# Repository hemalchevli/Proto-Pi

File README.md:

Proto-Pi
========

A simple prototyping board for Raspberry Pi with arduino headers
CC-BY-SA 4.0

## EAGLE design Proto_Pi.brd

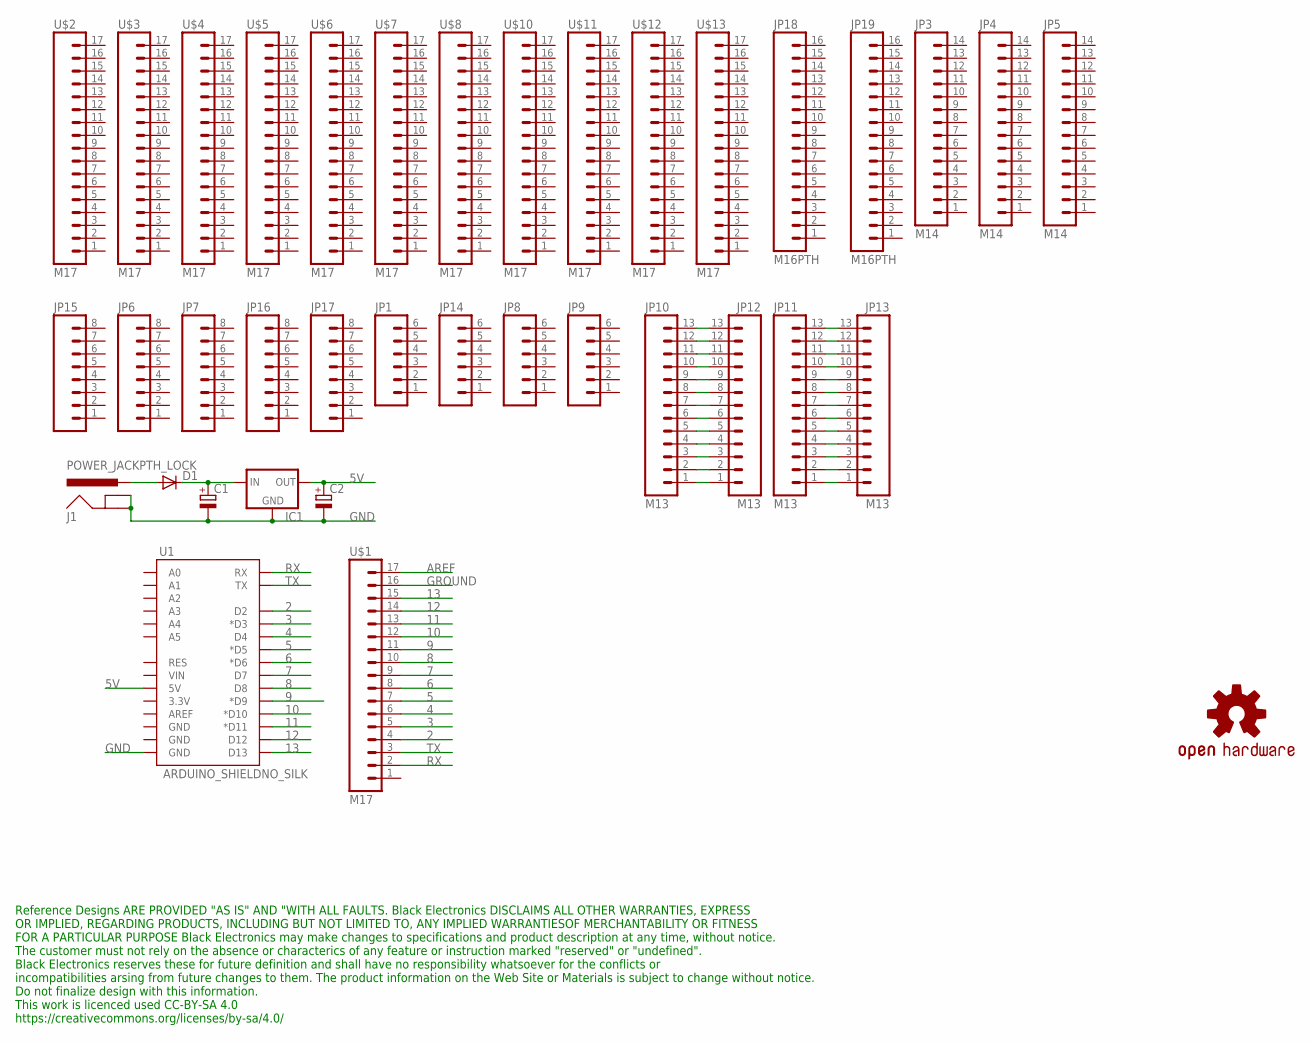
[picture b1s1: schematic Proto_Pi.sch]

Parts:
C1: CPOL-EUE2,5-6E; E2,5-6E
C2: CPOL-EUE2.5-7; E2,5-7
D1: DIODE-C1702-05; C1702-05
IC1: V_REG_78XXSINK; TO220-IGO
J1: POWER_JACKPTH_LOCK; POWER_JACK_PTH_LOCK
JP1, JP8, JP9, JP14: M06SIP; 1X06
JP3, JP4, JP5: M14; 1X14
JP6, JP7, JP15, JP16, JP17: M081X08; 1X08
JP10, JP11, JP12, JP13: M13; 1X13
JP18, JP19: M16PTH; 1X16
U1: ARDUINO_SHIELDNO_SILK; DUEMILANOVE_VIAS
U$1, U$2, U$3, U$4, U$5, U$6, U$7, U$8, U$10, U$11, U$12, U$13: M17; 1X17
U$9: OSHW-LOGOS; OSHW-LOGO-S

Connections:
2: U1.D2, U$1.4
3: U1.D3 (*D3), U$1.5
4: U1.D4, U$1.6
5: U1.D5 (*D5), U$1.7
5V: C2.+, IC1.OUT, U1.5V
6: U1.D6 (*D6), U$1.8
7: U1.D7, U$1.9
8: U1.D8, U$1.10
9: U1.D9 (*D9), U$1.11
10: U1.D10 (*D10), U$1.12
11: U1.D11 (*D11), U$1.13
12: U1.D12, U$1.14
13: U1.D13, U$1.15
AREF: U$1.17
GND: C1.-, C2.-, IC1.GND, J1.GND, J1.GNDBREAK, U1.GND@0 (GND)
GROUND: U$1.16
unnamed: JP10.1, JP12.1
unnamed: JP10.2, JP12.2
unnamed: JP10.3, JP12.3
unnamed: JP10.4, JP12.4
unnamed: JP10.5, JP12.5
unnamed: JP10.6, JP12.6
unnamed: JP10.7, JP12.7
unnamed: JP10.8, JP12.8
unnamed: JP10.9, JP12.9
unnamed: JP10.10, JP12.10
unnamed: JP10.11, JP12.11
unnamed: JP10.12, JP12.12
unnamed: JP10.13, JP12.13
unnamed: JP11.1, JP13.1
unnamed: JP11.2, JP13.2
unnamed: JP11.3, JP13.3
unnamed: JP11.4, JP13.4
unnamed: JP11.5, JP13.5
unnamed: JP11.6, JP13.6
unnamed: JP11.7, JP13.7
unnamed: JP11.8, JP13.8
unnamed: JP11.9, JP13.9
unnamed: JP11.10, JP13.10
unnamed: JP11.11, JP13.11
unnamed: JP11.12, JP13.12
unnamed: JP11.13, JP13.13
unnamed: C1.+, D1.C, IC1.IN
unnamed: D1.A, J1.PWR
RX: U1.RX, U$1.2
TX: U1.TX, U$1.3

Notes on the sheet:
Reference Designs ARE PROVIDED "AS IS" AND "WITH ALL FAULTS. Black Electronics DISCLAIMS ALL OTHER WARRANTIES, EXPRESS OR IMPLIED, REGARDING PRODUCTS, INCLUDING BUT NOT LIMITED TO, ANY IMPLIED WARRANTIESOF MERCHANTABILITY OR FITNESS FOR A PARTICULAR PURPOSE Black Electronics may make changes to spe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

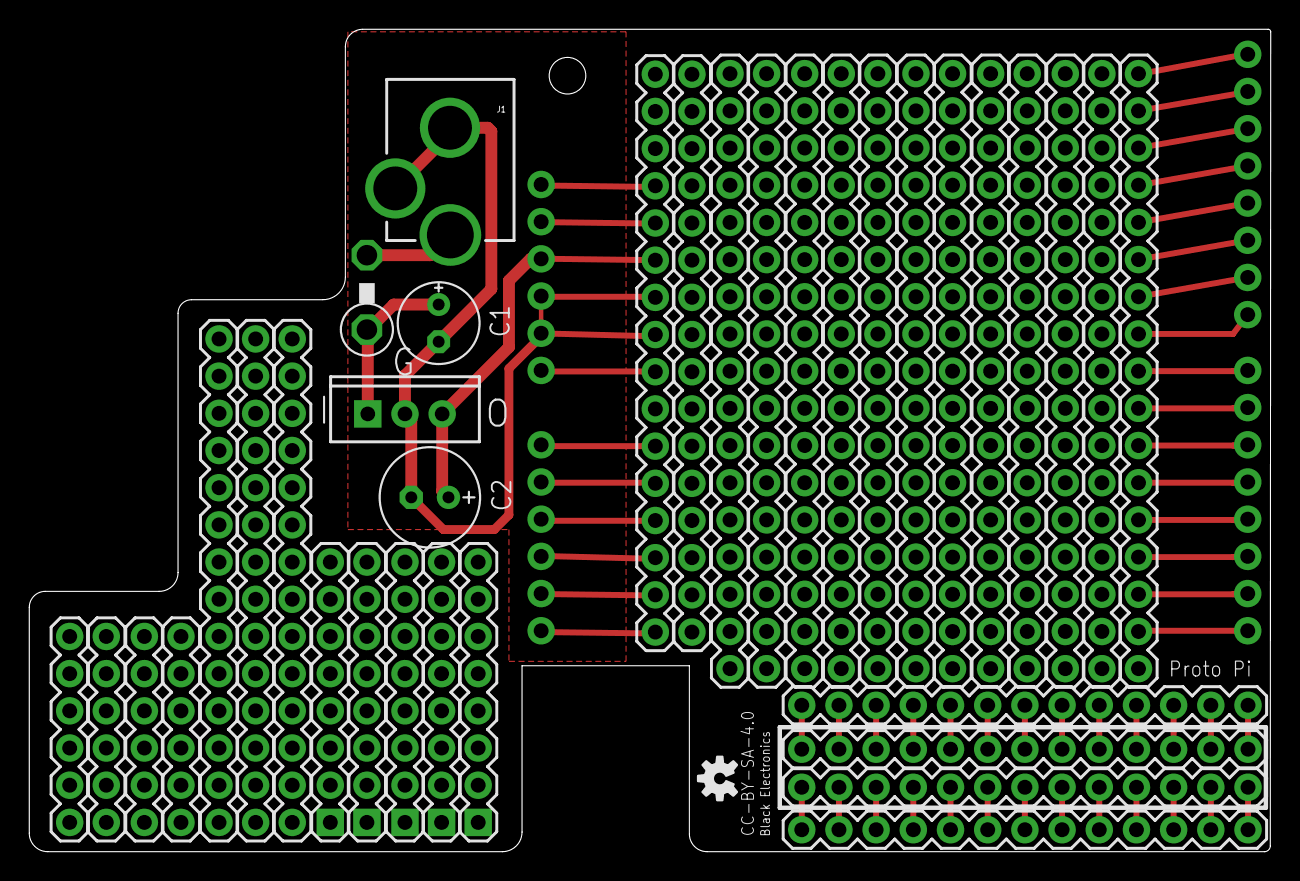
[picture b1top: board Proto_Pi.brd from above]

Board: 2 copper layers, 84.8 x 56.2 mm, 37 parts (0 on the bottom side), 44 nets.

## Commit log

2014-07-07 Added PS
2014-07-07 Tidy up
2014-07-07 logo licence name

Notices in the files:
Proto_Pi.sch:
This work is licenced used CC-BY-SA 4.0
https://creativecommons.org/licenses/by-sa/4.0
parts and their libraries:
SparkFun: Licensing: CC v3.0 Share-Alike You are welcome to use this library for commercial purposes.
